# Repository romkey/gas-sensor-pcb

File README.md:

# gas-sensor-pcb
Open source gas sensor add-on for furball. This board takes up to four 5V MQ-series gas sensor breakout boards and makes them available over I2C using an ADC and levelshifter.

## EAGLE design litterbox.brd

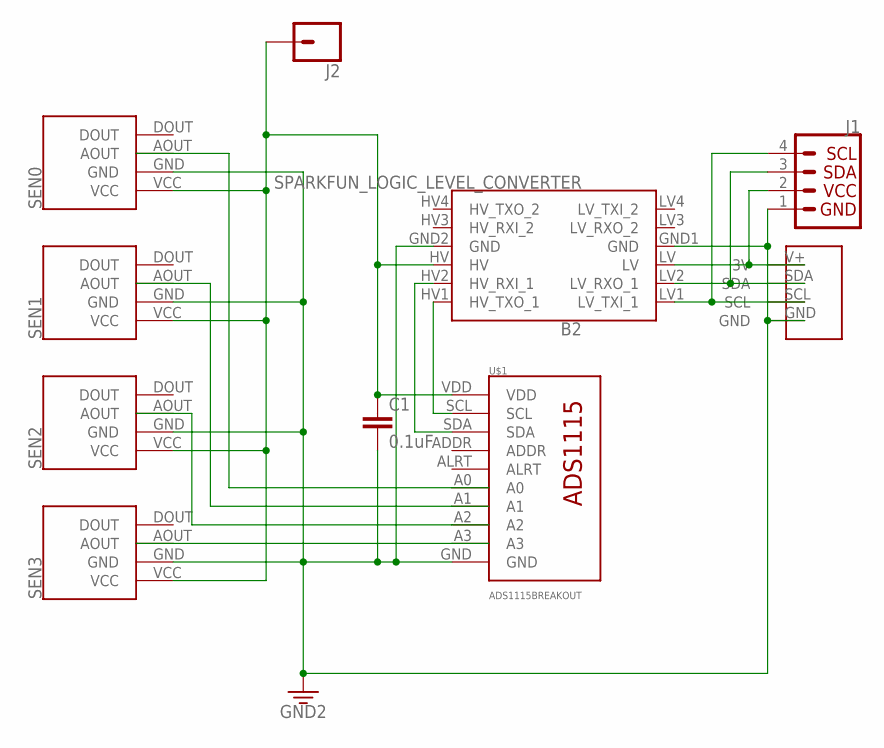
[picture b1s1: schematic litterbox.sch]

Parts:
B2: SPARKFUN_LOGIC_LEVEL_CONVERTER
C1: 0.1uF; CAP-PTH-SMALL-KIT
J1: QWIIC_CONNECTORJS-1MM; 1X04_1MM_RA
J2: CONN_01; 1X01
SEN0, SEN1, SEN2, SEN3: MQ-SENSOR-BREAKOUT
U$1: ADS1115BREAKOUT
U$2: I2CHEADER

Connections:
3V3: B2.LV, J1.2 (VCC), U$2.V+ (3V)
5V: B2.HV, C1.1, J2.1, SEN0.VCC, SEN1.VCC, SEN2.VCC, SEN3.VCC, U$1.VDD
GND: B2.GND1 (GND), B2.GND2 (GND), C1.2, J1.1 (GND), SEN0.GND, SEN1.GND, SEN2.GND, SEN3.GND, U$1.GND, U$2.GND
unnamed: B2.HV2 (HV_RXI_1), U$1.SDA
unnamed: B2.LV1 (LV_TXI_1), J1.4 (SCL), U$2.SCL
unnamed: B2.HV1 (HV_TXO_1), U$1.SCL
unnamed: B2.LV2 (LV_RXO_1), J1.3 (SDA), U$2.SDA
SEN0A: SEN3.AOUT, U$1.A3
SEN1A: SEN2.AOUT, U$1.A2
SEN3A: SEN1.AOUT, U$1.A1
SEN4A: SEN0.AOUT, U$1.A0

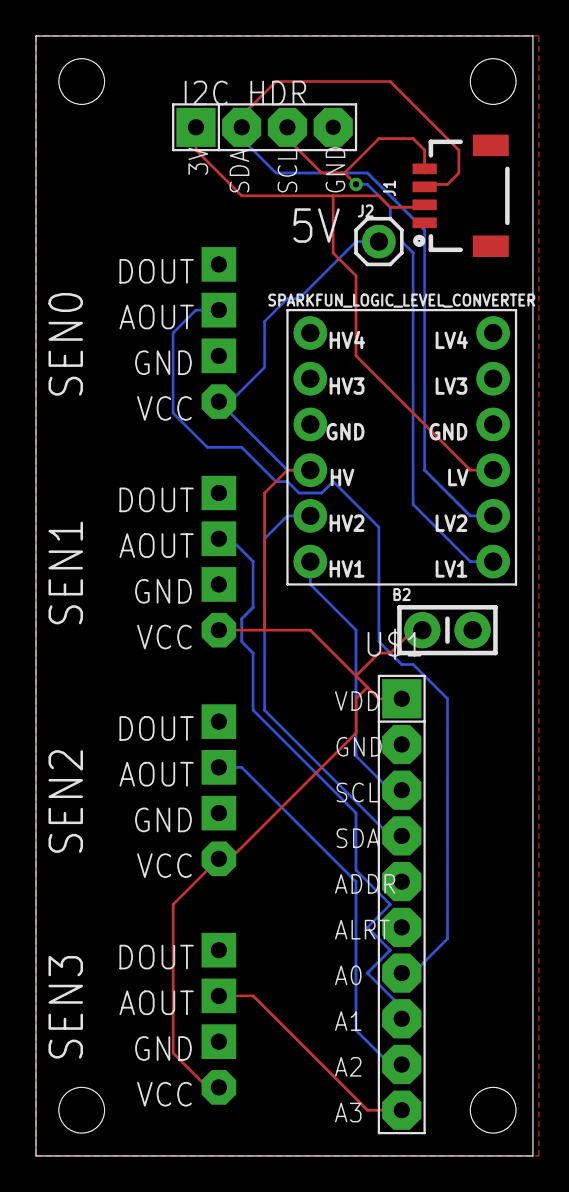
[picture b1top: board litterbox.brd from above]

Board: 2 copper layers, 27.6 x 62.2 mm, 11 parts (1 on the bottom side), 11 nets.

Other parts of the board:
U$3: OSHW-LOGO-L

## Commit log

2019-12-11 eagle schematic and board layout

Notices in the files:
parts and their libraries:
SparkFun-Capacitors: Licensing: Creative Commons ShareAlike 4.0 International - https://creativecommons.org/licenses/by-sa/4.0
